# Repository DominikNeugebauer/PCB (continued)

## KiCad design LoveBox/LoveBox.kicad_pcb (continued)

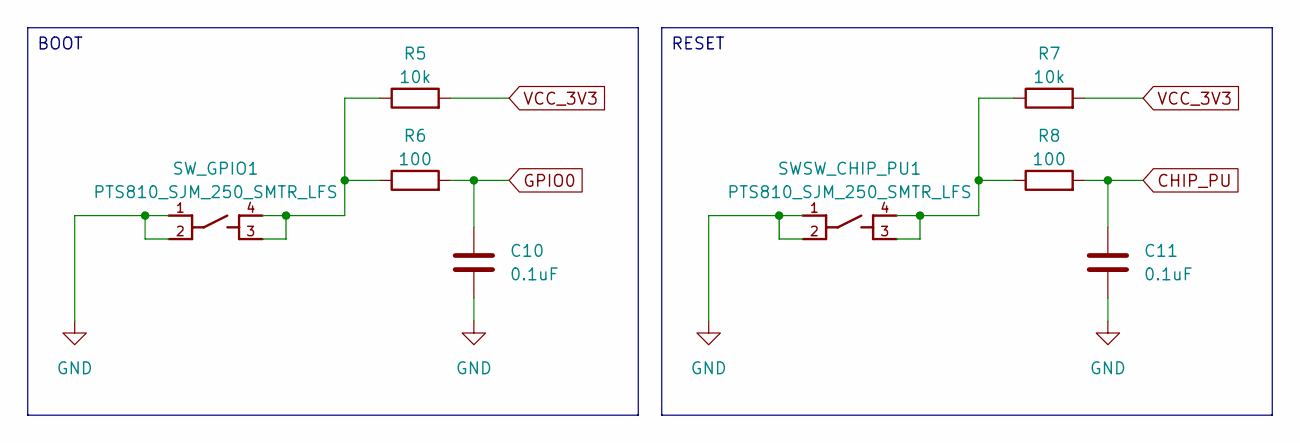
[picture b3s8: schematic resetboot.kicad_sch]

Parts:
C10, C11: 0.1uF; C_0603_1608Metric
R5, R7: 10k; R_0603_1608Metric
R6, R8: 100; R_0603_1608Metric
SWSW_CHIP_PU1: PTS810_SJM_250_SMTR_LFS
SW_GPIO1: PTS810_SJM_250_SMTR_LFS

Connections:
CHIP_PU: C11.1, R8.2; also elsewhere on the board
GND: C10.2, C11.2, SWSW_CHIP_PU1.1, SWSW_CHIP_PU1.2, SW_GPIO1.1, SW_GPIO1.2; also elsewhere on the board
GPIO0: C10.1, R6.2; also elsewhere on the board
unnamed 22: R5.1, R6.1, SW_GPIO1.3, SW_GPIO1.4; also elsewhere on the board
unnamed 23: R7.1, R8.1, SWSW_CHIP_PU1.3, SWSW_CHIP_PU1.4; also elsewhere on the board
VCC_3V3: R5.2, R7.2; also elsewhere on the board

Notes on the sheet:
RESET
BOOT

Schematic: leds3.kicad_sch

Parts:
C25, C38, C39, C40, C41, C42, C43, C44, C45, C46: 100nF; C_0603_1608Metric
R31: 330; R_0603_1608Metric
U27, U28, U29, U30, U31, U32, U33, U34, U35, U36: WS2812B; WS2812B_WDS

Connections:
GND: C25.2, C38.2, C39.2, C40.2, C41.2, C42.2, C43.2, C44.2, C45.2, C46.2, U27.3 (VSS), U28.3 (VSS), U29.3 (VSS), U30.3 (VSS), U31.3 (VSS), U32.3 (VSS), U33.3 (VSS), U34.3 (VSS), U35.3 (VSS), U36.3 (VSS); also elsewhere on the board
LEDS3: R31.1; also elsewhere on the board
LEDS4: U36.2 (DOUT); also elsewhere on the board
unnamed: R31.2, U27.4 (DIN)
unnamed: U27.2 (DOUT), U30.4 (DIN)
unnamed: U28.2 (DOUT), U31.4 (DIN)
unnamed: U29.2 (DOUT), U32.4 (DIN)
unnamed: U30.2 (DOUT), U33.4 (DIN)
unnamed: U31.2 (DOUT), U34.4 (DIN)
unnamed: U32.2 (DOUT), U35.4 (DIN)
unnamed: U35.2 (DOUT), U36.4 (DIN)
RE6: U28.4 (DIN), U33.2 (DOUT)
RE7: U29.4 (DIN), U34.2 (DOUT)
VCC_3V3: C25.1, C38.1, C39.1, C40.1, C41.1, C42.1, C43.1, C44.1, C45.1, C46.1, U27.1 (VDD), U28.1 (VDD), U29.1 (VDD), U30.1 (VDD), U31.1 (VDD), U32.1 (VDD), U33.1 (VDD), U34.1 (VDD), U35.1 (VDD), U36.1 (VDD); also elsewhere on the board

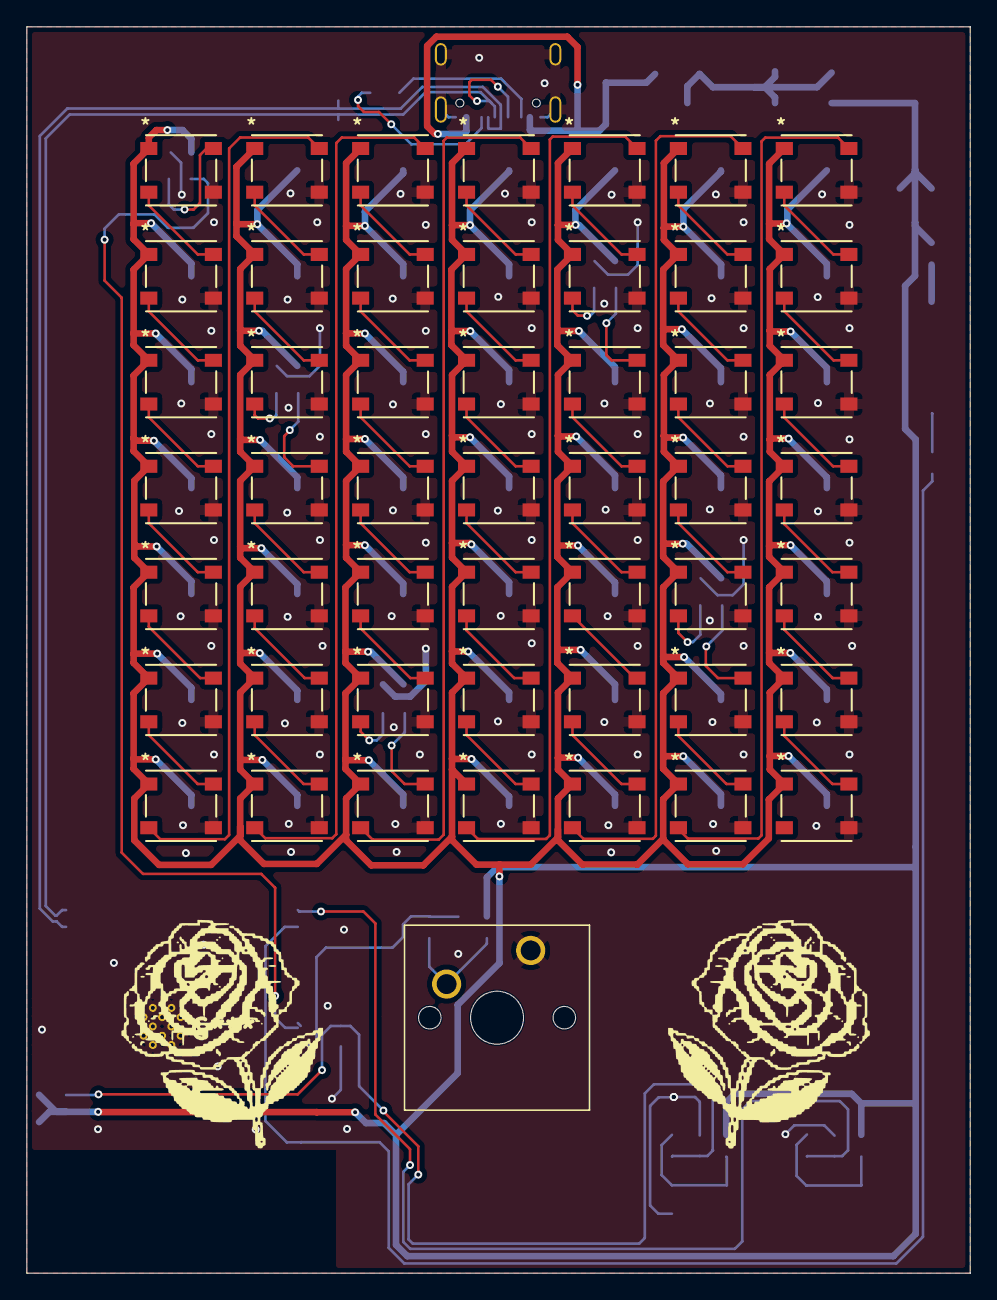
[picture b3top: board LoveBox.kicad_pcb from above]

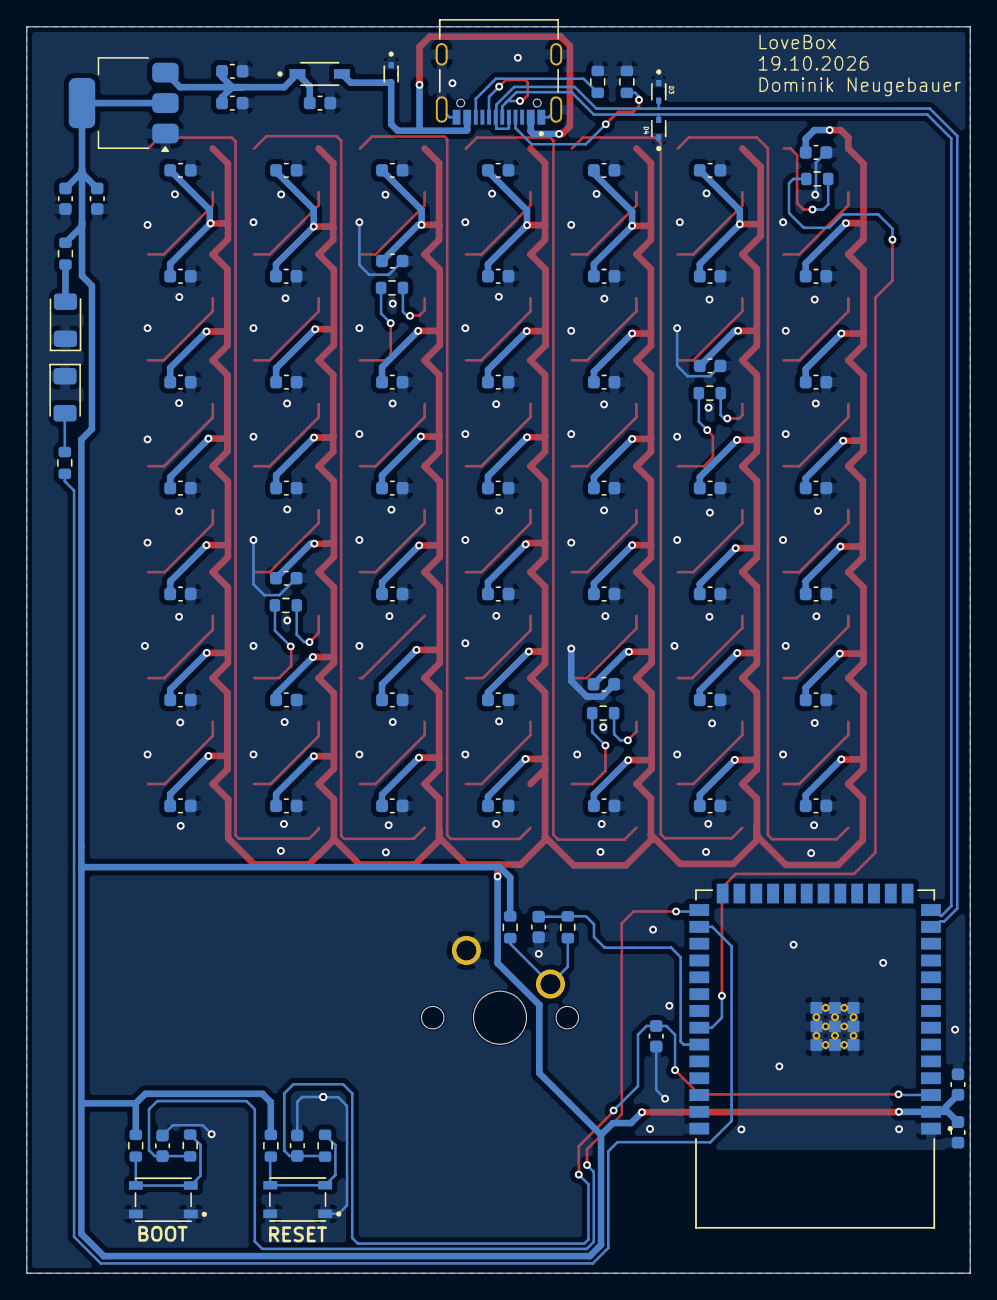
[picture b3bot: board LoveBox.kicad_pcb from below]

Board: 2 copper layers, 71.3 x 94.1 mm, 136 parts (86 on the bottom side), 71 nets.

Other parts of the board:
BOOT: PTS810_SJM_250_SMTR_LFS
RESET: PTS810_SJM_250_SMTR_LFS

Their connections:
GND: BOOT.1, BOOT.2, RESET.1, RESET.2; also elsewhere on the board
unnamed 22: BOOT.3, BOOT.4; also elsewhere on the board
unnamed 23: RESET.3, RESET.4; also elsewhere on the board

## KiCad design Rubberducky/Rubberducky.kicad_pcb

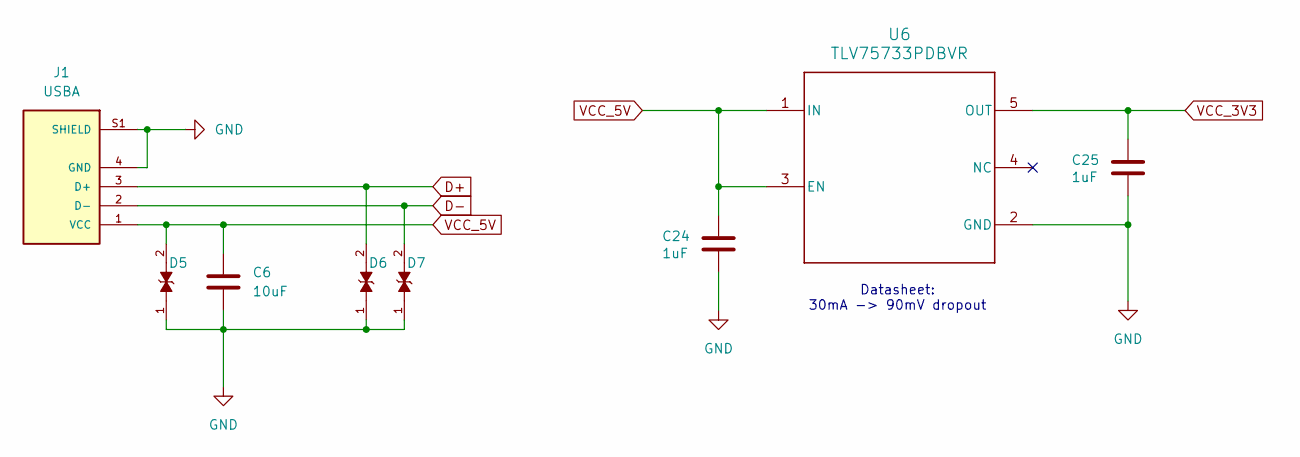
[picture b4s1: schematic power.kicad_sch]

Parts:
C6: 10uF; C_0603_1608Metric
C24, C25: 1uF; C_0603_1608Metric
D5, D6, D7: LESD5D5.0CT1G; PARTREV O
J1: USBA; USBA_Male_SMD; PARTREV D
U6: TLV75733PDBVR; SOT95P280X145-5N_TLV75733PDBVR

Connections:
D+: D6.2, J1.3 (D+); also elsewhere on the board
D-: D7.2, J1.2 (D-); also elsewhere on the board
GND: C6.2, C24.2, C25.2, D5.1, D6.1, D7.1, J1.4 (GND), J1.S1 (SHIELD), J1.S2 (SHIELD), U6.2 (GND); also elsewhere on the board
VCC_3V3: C25.1, U6.5 (OUT); also elsewhere on the board
VCC_5V: C6.1, C24.1, D5.2, J1.1 (VCC), U6.1 (IN), U6.3 (EN)

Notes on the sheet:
Datasheet: 30mA -> 90mV dropout

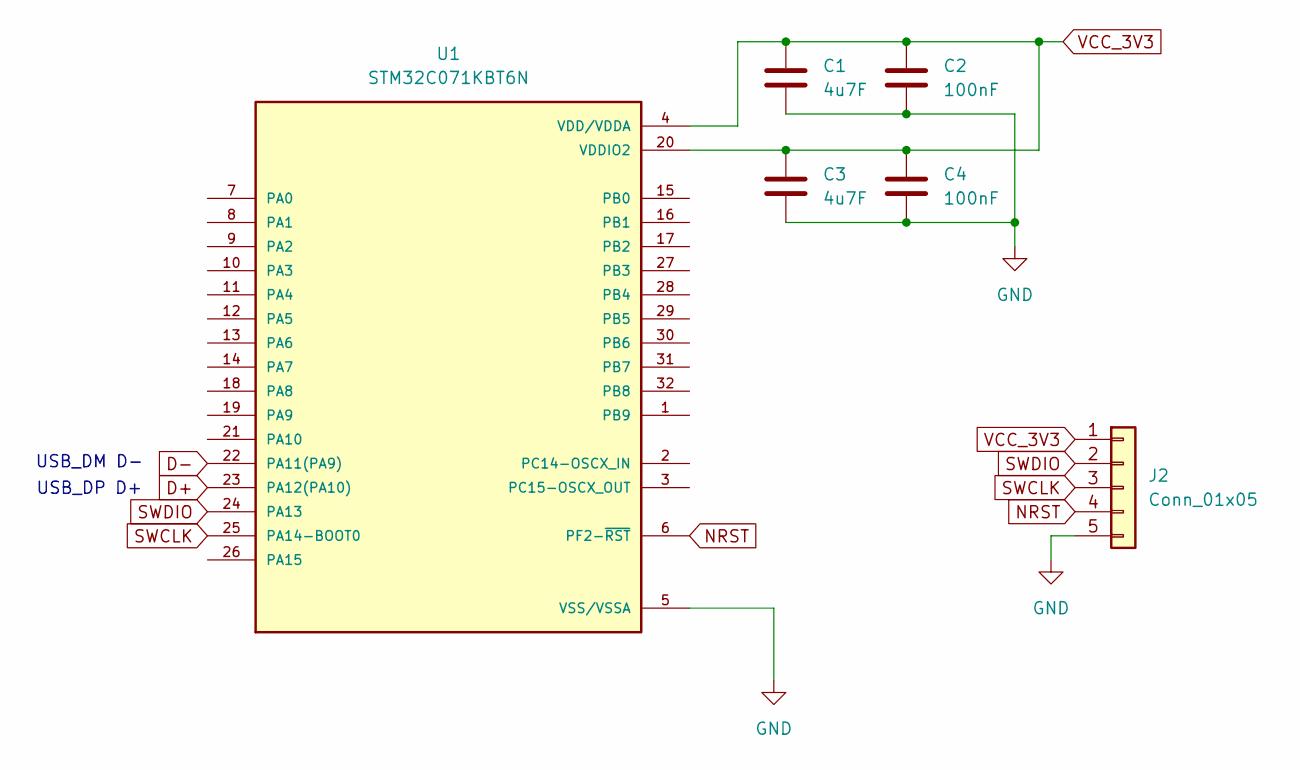
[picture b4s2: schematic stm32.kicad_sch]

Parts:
C1, C3: 4u7F; C_0603_1608Metric
C2, C4: 100nF; C_0603_1608Metric
J2: Conn_01x05; PinHeader_1x05_P2.54mm_Vertical
U1: STM32C071KBT6N; PARTREV 1

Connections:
D+: U1.23 (PA12(PA10)); also elsewhere on the board
D-: U1.22 (PA11(PA9)); also elsewhere on the board
GND: C1.2, C2.2, C3.2, C4.2, J2.5, U1.5 (VSS/VSSA); also elsewhere on the board
NRST: J2.4, U1.6 (PF2-~RST)
SWCLK: J2.3, U1.25 (PA14-BOOT0)
SWDIO: J2.2, U1.24 (PA13)
VCC_3V3: C1.1, C2.1, C3.1, C4.1, J2.1, U1.4 (VDD/VDDA), U1.20 (VDDIO2); also elsewhere on the board

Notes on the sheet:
USB_DM D-
USB_DP D+

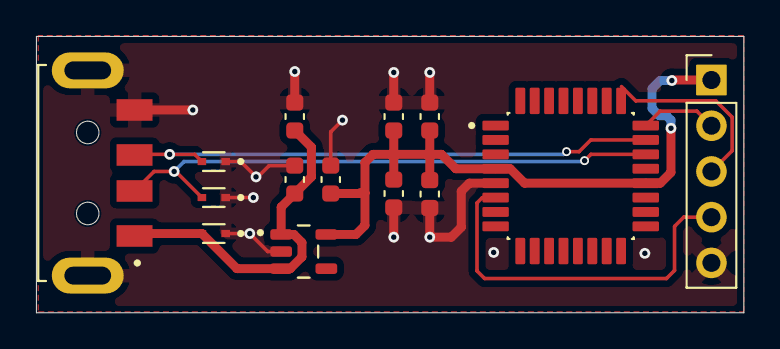
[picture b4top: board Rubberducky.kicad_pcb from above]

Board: 2 copper layers, 39.3 x 15.4 mm, 14 parts (0 on the bottom side), 8 nets.

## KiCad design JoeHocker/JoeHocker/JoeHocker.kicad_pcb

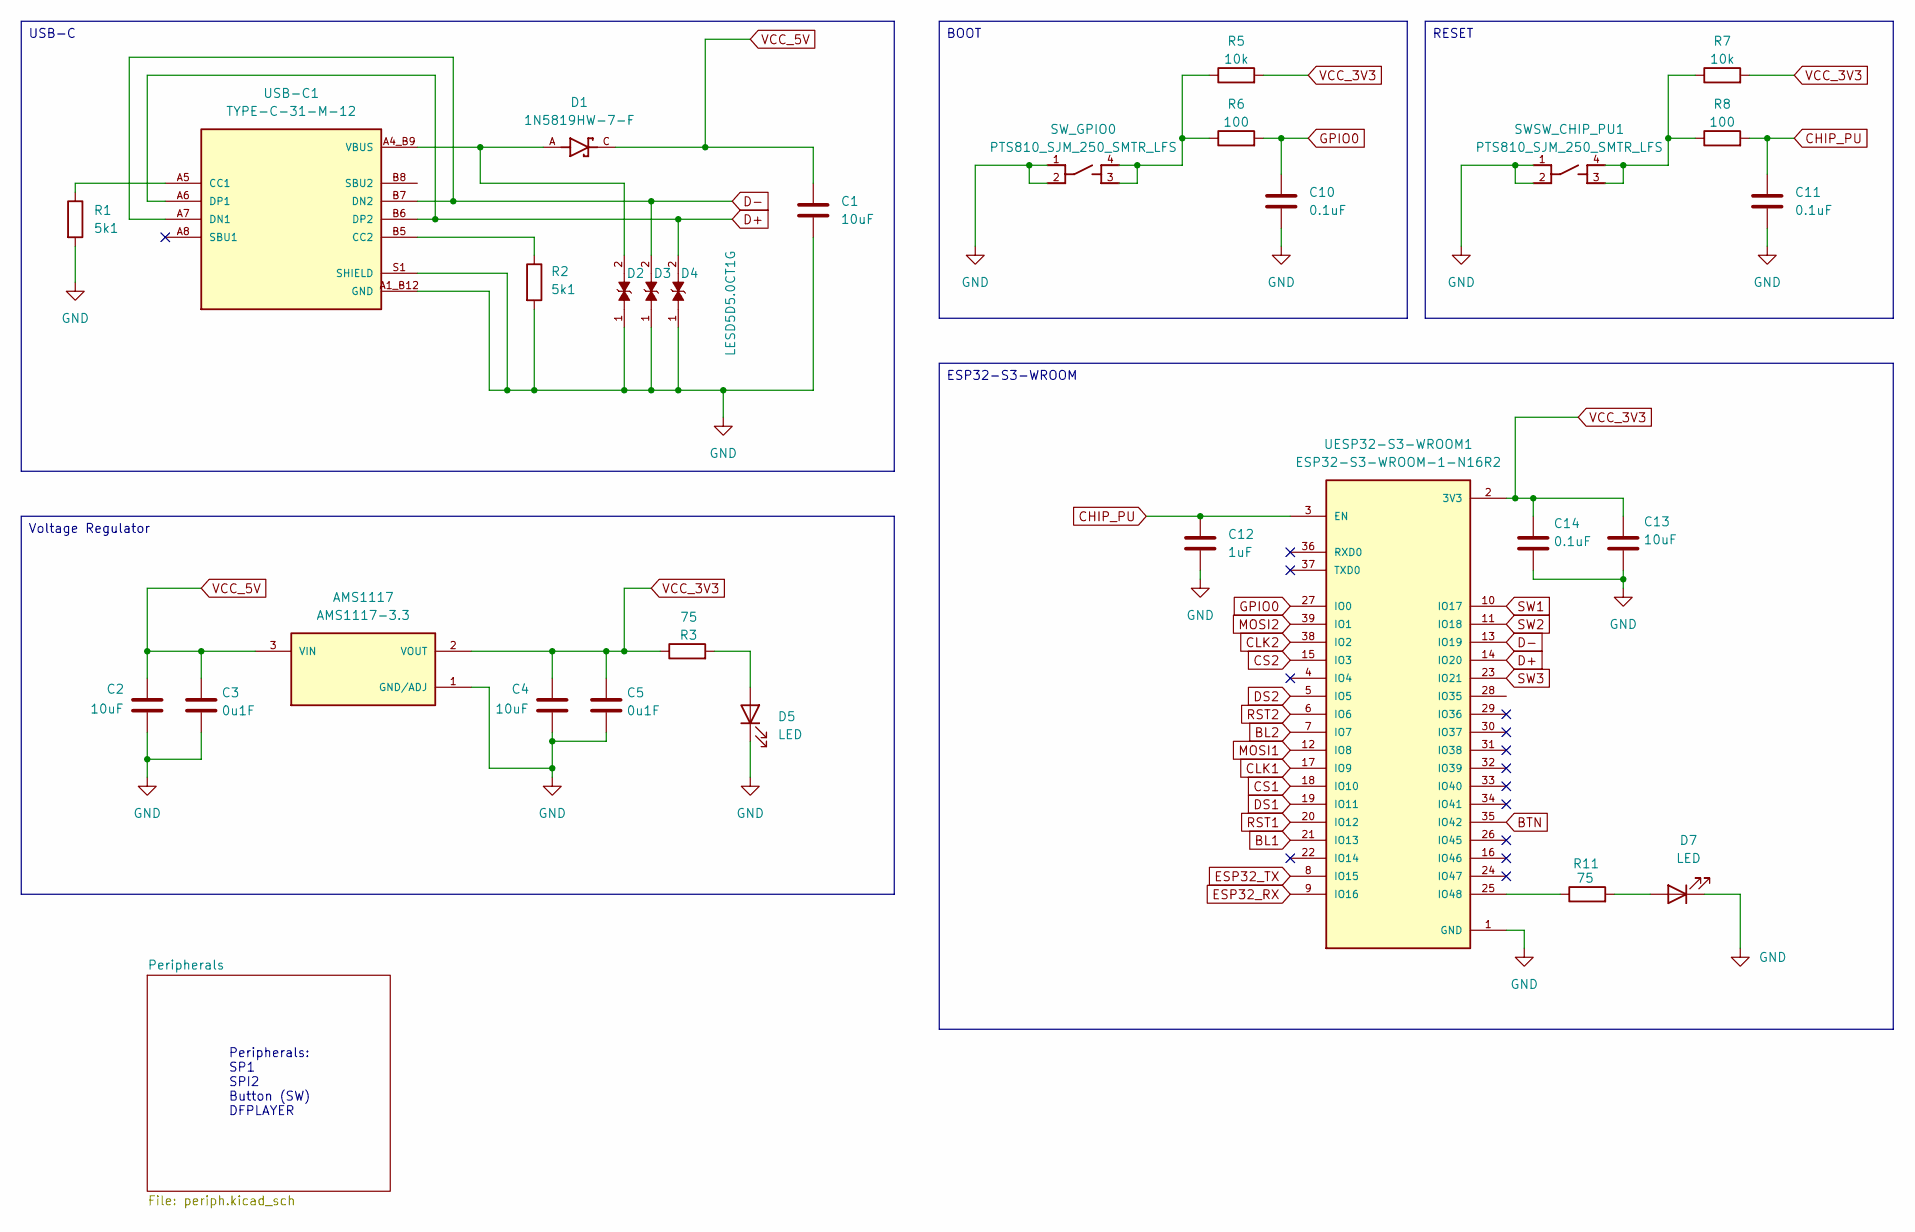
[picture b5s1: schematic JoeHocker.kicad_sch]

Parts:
AMS1117: AMS1117-3.3; SOT-223-3_TabPin2; PARTREV N/A
C1, C2, C4, C13: 10uF; C_0603_1608Metric
C3, C5: 0u1F; C_0603_1608Metric
C10, C11, C14: 0.1uF; C_0603_1608Metric
C12: 1uF; C_0603_1608Metric
D1: 1N5819HW-7-F; SOD3715X145N; PARTREV 18-2
D2, D3, D4: LESD5D5.0CT1G; TVS_LESD5D5.0CT1G; PARTREV O
D5, D7: LED; LED_1206_3216Metric
R1, R2: 5k1; R_0603_1608Metric
R3, R11: 75; R_0603_1608Metric
R5, R7: 10k; R_0603_1608Metric
R6, R8: 100; R_0603_1608Metric
SWSW_CHIP_PU1: PTS810_SJM_250_SMTR_LFS; SW_PTS810_SJM_250_SMTR_LFS
SW_GPIO0: PTS810_SJM_250_SMTR_LFS; SW_PTS810_SJM_250_SMTR_LFS
UESP32-S3-WROOM1: ESP32-S3-WROOM-1-N16R2; ESP32_S3_WROOM_N16R2_CUSTOM; PARTREV v1.0
USB-C1: TYPE-C-31-M-12; HRO_TYPE-C-31-M-12; PARTREV 2020.12.08

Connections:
BL1: UESP32-S3-WROOM1.21 (IO13); also elsewhere on the board
BL2: UESP32-S3-WROOM1.7 (IO7); also elsewhere on the board
BTN: UESP32-S3-WROOM1.35 (IO42); also elsewhere on the board
CHIP_PU: C11.1, C12.1, R8.2, UESP32-S3-WROOM1.3 (EN)
CLK1: UESP32-S3-WROOM1.17 (IO9); also elsewhere on the board
CLK2: UESP32-S3-WROOM1.38 (IO2); also elsewhere on the board
CS1: UESP32-S3-WROOM1.18 (IO10); also elsewhere on the board
CS2: UESP32-S3-WROOM1.15 (IO3); also elsewhere on the board
D+: D4.2, UESP32-S3-WROOM1.14 (IO20), USB-C1.A6 (DP1), USB-C1.B6 (DP2)
D-: D3.2, UESP32-S3-WROOM1.13 (IO19), USB-C1.A7 (DN1), USB-C1.B7 (DN2)
DS1: UESP32-S3-WROOM1.19 (IO11); also elsewhere on the board
DS2: UESP32-S3-WROOM1.5 (IO5); also elsewhere on the board
ESP32_RX: UESP32-S3-WROOM1.9 (IO16); also elsewhere on the board
ESP32_TX: UESP32-S3-WROOM1.8 (IO15); also elsewhere on the board
GND: AMS1117.1 (GND/ADJ), C1.2, C2.2, C3.2, C4.2, C5.2, C10.2, C11.2, C12.2, C13.2, C14.2, D2.1, D3.1, D4.1, D5.1 (K), D7.1 (K), R1.2, R2.2, SWSW_CHIP_PU1.1, SWSW_CHIP_PU1.2, SW_GPIO0.1, SW_GPIO0.2, UESP32-S3-WROOM1.1 (GND), UESP32-S3-WROOM1.40 (GND), UESP32-S3-WROOM1.41_1 (GND), UESP32-S3-WROOM1.41_2 (GND), UESP32-S3-WROOM1.41_3 (GND), UESP32-S3-WROOM1.41_4 (GND), UESP32-S3-WROOM1.41_5 (GND), UESP32-S3-WROOM1.41_6 (GND), UESP32-S3-WROOM1.41_7 (GND), UESP32-S3-WROOM1.41_8 (GND), UESP32-S3-WROOM1.41_9 (GND), UESP32-S3-WROOM1.41_10, UESP32-S3-WROOM1.41_11, UESP32-S3-WROOM1.41_12, UESP32-S3-WROOM1.41_13, UESP32-S3-WROOM1.41_14, UESP32-S3-WROOM1.41_15, UESP32-S3-WROOM1.41_16, UESP32-S3-WROOM1.41_17, UESP32-S3-WROOM1.41_18, UESP32-S3-WROOM1.41_19, UESP32-S3-WROOM1.41_20, UESP32-S3-WROOM1.41_21, USB-C1.A1_B12 (GND), USB-C1.B1_A12 (GND), USB-C1.S1 (SHIELD), USB-C1.S2 (SHIELD), USB-C1.S3 (SHIELD), USB-C1.S4 (SHIELD); also elsewhere on the board
GPIO0: C10.1, R6.2, UESP32-S3-WROOM1.27 (IO0)
MOSI1: UESP32-S3-WROOM1.12 (IO8); also elsewhere on the board
MOSI2: UESP32-S3-WROOM1.39 (IO1); also elsewhere on the board
unnamed: D5.2 (A), R3.2
unnamed: D7.2 (A), R11.2
unnamed 22: R5.1, R6.1, SW_GPIO0.3, SW_GPIO0.4; also elsewhere on the board
unnamed 23: R7.1, R8.1, SWSW_CHIP_PU1.3, SWSW_CHIP_PU1.4; also elsewhere on the board
unnamed: R11.1, UESP32-S3-WROOM1.25 (IO48)
unnamed: R1.1, USB-C1.A5 (CC1)
unnamed: R2.1, USB-C1.B5 (CC2)
RST1: UESP32-S3-WROOM1.20 (IO12); also elsewhere on the board
RST2: UESP32-S3-WROOM1.6 (IO6); also elsewhere on the board
SW1: UESP32-S3-WROOM1.10 (IO17); also elsewhere on the board
SW2: UESP32-S3-WROOM1.11 (IO18); also elsewhere on the board
SW3: UESP32-S3-WROOM1.23 (IO21); also elsewhere on the board
VBUS: D1.A, D2.2, USB-C1.A4_B9 (VBUS), USB-C1.B4_A9 (VBUS)
VCC_3V3: AMS1117.2 (VOUT), C4.1, C5.1, C13.1, C14.1, R3.1, R5.2, R7.2, UESP32-S3-WROOM1.2 (3V3); also elsewhere on the board
VCC_5V: AMS1117.3 (VIN), C1.1, C2.1, C3.1, D1.C

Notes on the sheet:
Peripherals: SP1 SPI2 Button (SW) DFPLAYER
BOOT
ESP32-S3-WROOM
Voltage Regulator
RESET
USB-C

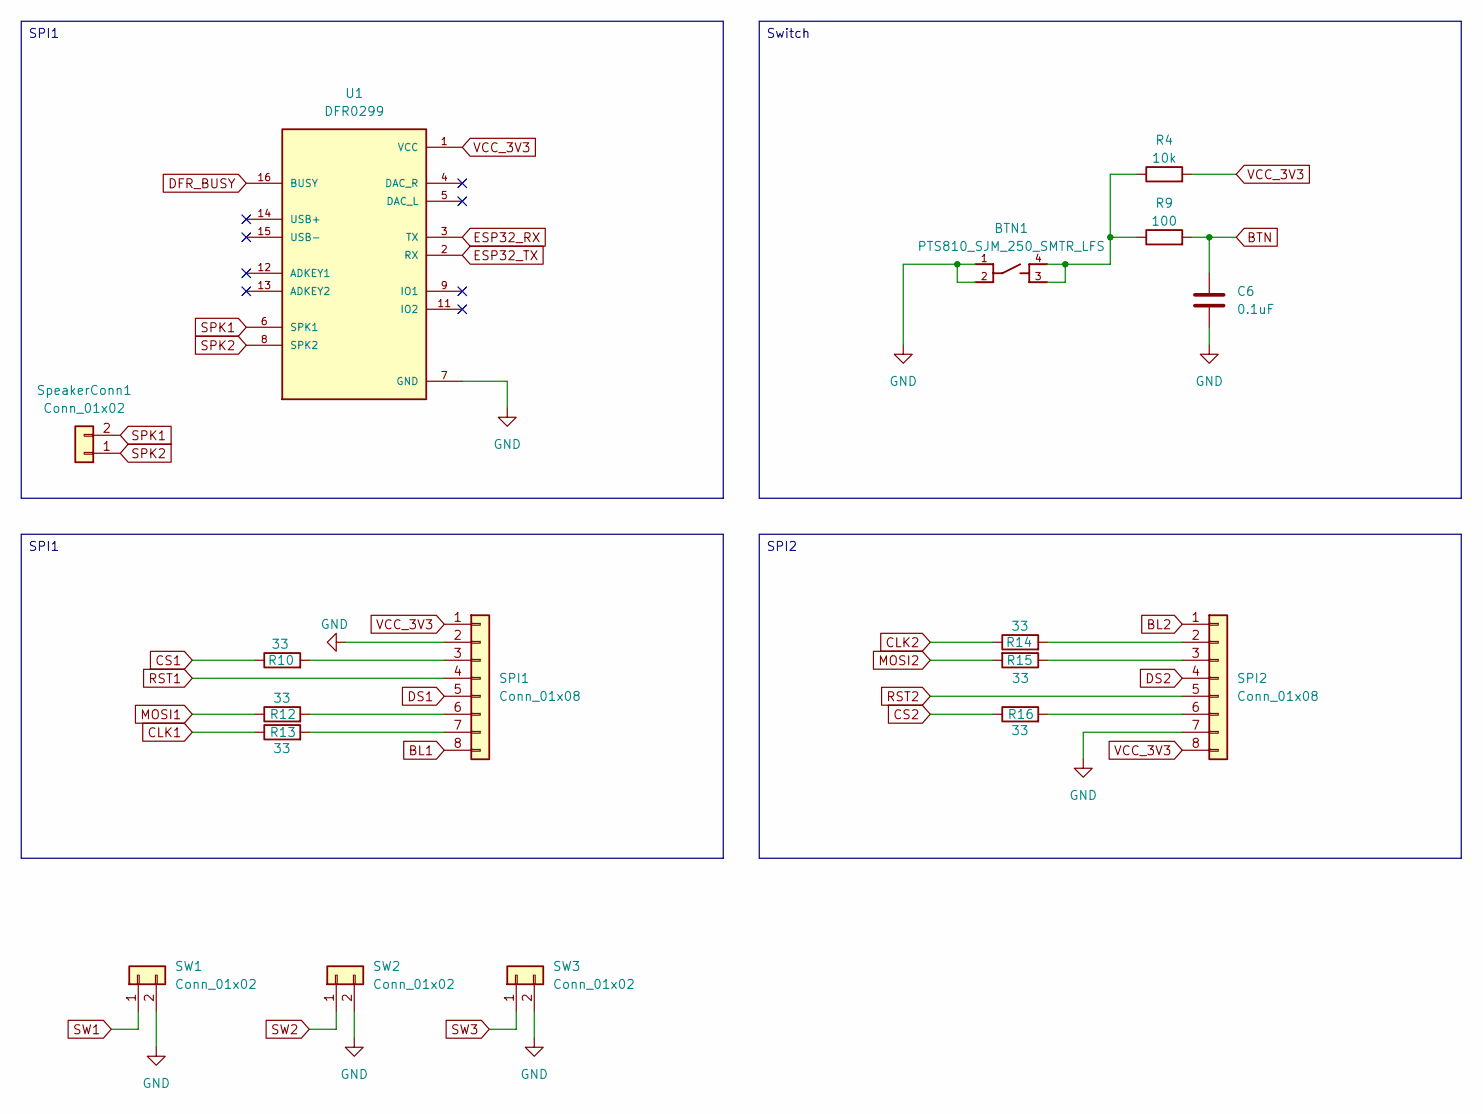
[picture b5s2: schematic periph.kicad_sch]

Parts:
BTN1: PTS810_SJM_250_SMTR_LFS; SW_PTS810_SJM_250_SMTR_LFS
C6: 0.1uF; C_0603_1608Metric
R4: 10k; R_0603_1608Metric
R9: 100; R_0603_1608Metric
R10, R12, R13, R14, R15, R16: 33; R_0603_1608Metric
SPI1, SPI2: Conn_01x08; PinHeader_1x08_P2.54mm_Vertical
SW1, SW2, SW3: Conn_01x02; PinHeader_1x02_P2.54mm_Vertical
SpeakerConn1: Conn_01x02; PinHeader_1x02_P2.54mm_Vertical
U1: DFR0299; MODULE_DFR029_DFPLAYER

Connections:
BL1: SPI1.8; also elsewhere on the board
BL2: SPI2.1; also elsewhere on the board
BTN: C6.1, R9.2; also elsewhere on the board
CLK1: R13.1; also elsewhere on the board
CLK2: R14.1; also elsewhere on the board
CS1: R10.1; also elsewhere on the board
CS2: R16.1; also elsewhere on the board
DFR_BUSY: U1.16 (BUSY)
DS1: SPI1.5; also elsewhere on the board
DS2: SPI2.4; also elsewhere on the board
ESP32_RX: U1.3 (TX); also elsewhere on the board
ESP32_TX: U1.2 (RX); also elsewhere on the board
GND: BTN1.1, BTN1.2, C6.2, SPI1.2, SPI2.7, SW1.2, SW2.2, SW3.2, U1.7 (GND), U1.10 (GND); also elsewhere on the board
MOSI1: R12.1; also elsewhere on the board
MOSI2: R15.2; also elsewhere on the board
unnamed 19: BTN1.3, BTN1.4, R4.1, R9.1; also elsewhere on the board
unnamed: R10.2, SPI1.3
unnamed: R12.2, SPI1.6
unnamed: R13.2, SPI1.7
unnamed: R14.2, SPI2.2
unnamed: R15.1, SPI2.3
unnamed: R16.2, SPI2.6
RST1: SPI1.4; also elsewhere on the board
RST2: SPI2.5; also elsewhere on the board
SPK1: SpeakerConn1.2, U1.6 (SPK1)
SPK2: SpeakerConn1.1, U1.8 (SPK2)
SW1: SW1.1; also elsewhere on the board
SW2: SW2.1; also elsewhere on the board
SW3: SW3.1; also elsewhere on the board
VCC_3V3: R4.2, SPI1.1, SPI2.8, U1.1 (VCC); also elsewhere on the board

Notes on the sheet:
SPI1
SPI2
Switch

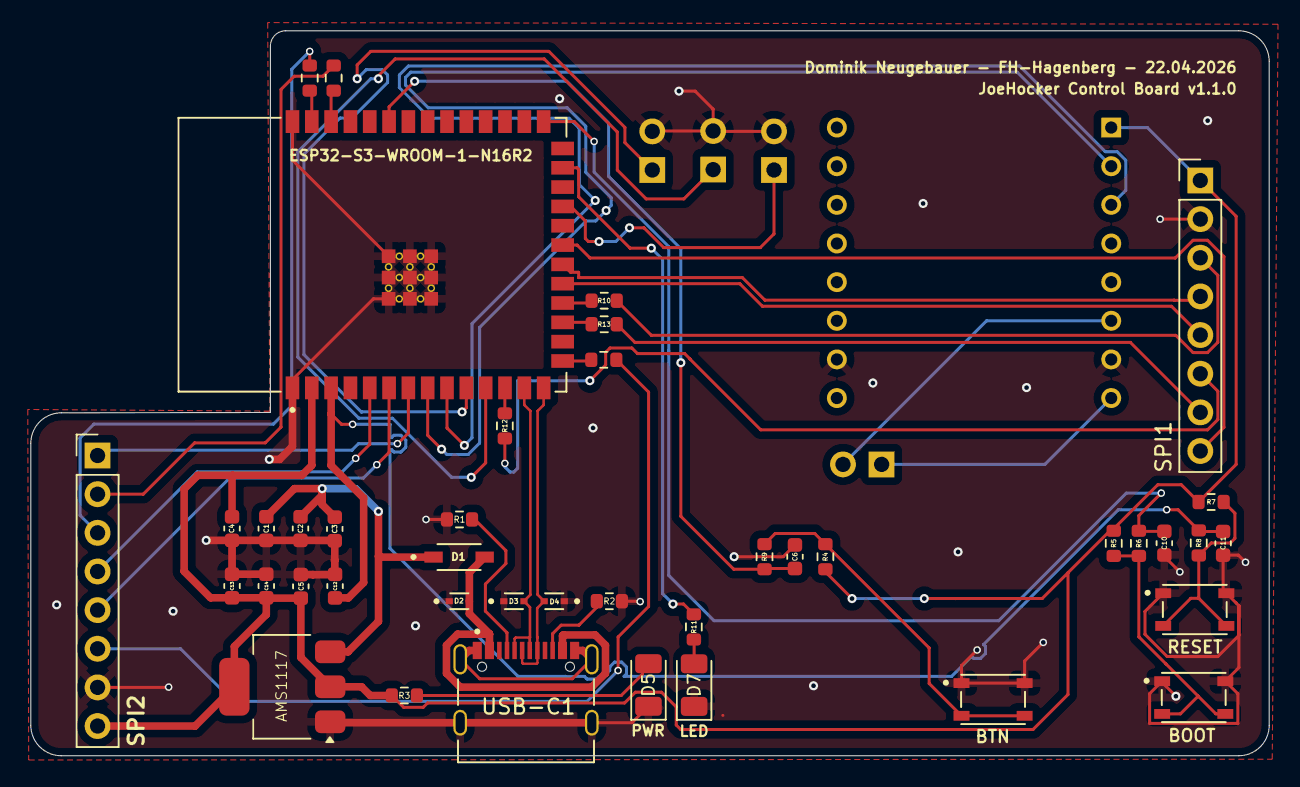
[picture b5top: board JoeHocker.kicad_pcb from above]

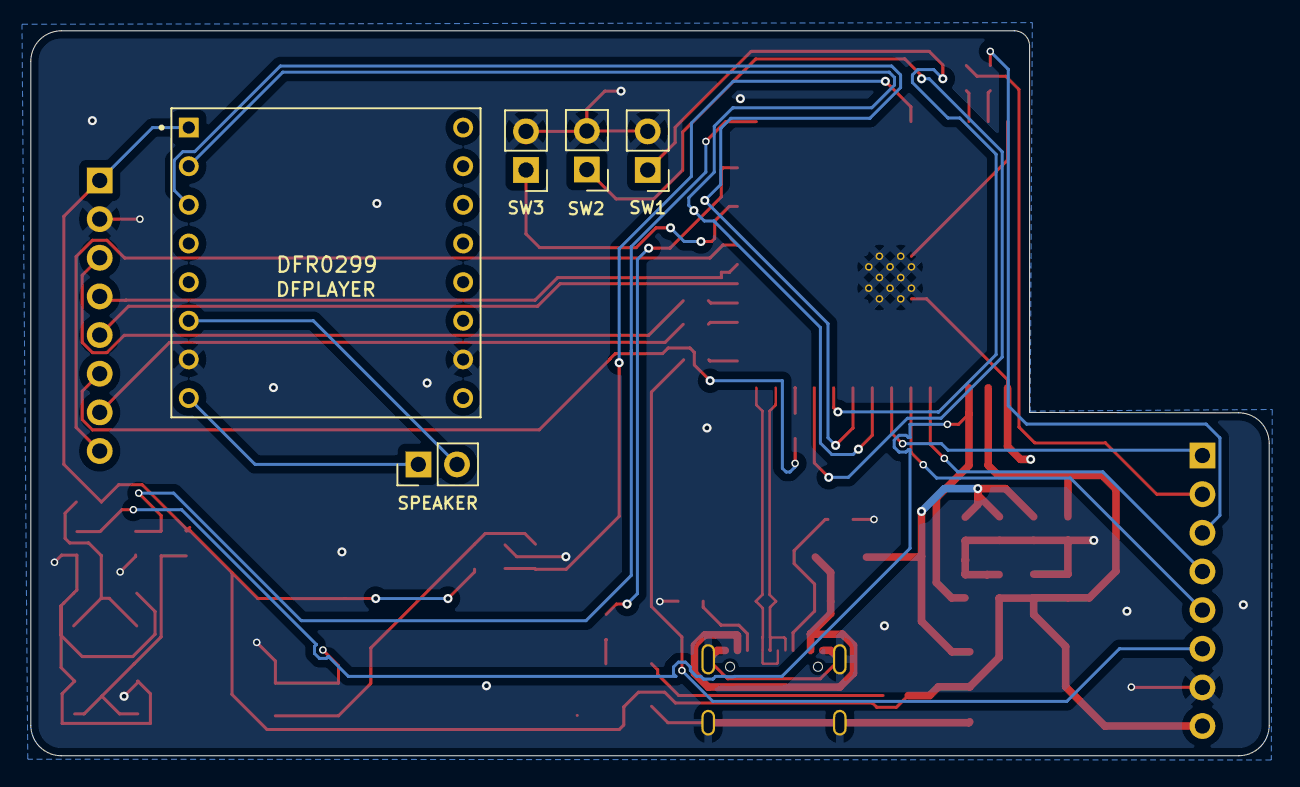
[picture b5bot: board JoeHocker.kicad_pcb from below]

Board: 4 copper layers, 81.4 x 47.6 mm, 46 parts (5 on the bottom side), 42 nets.

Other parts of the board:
BOOT: PTS810_SJM_250_SMTR_LFS; SW_PTS810_SJM_250_SMTR_LFS
BTN: PTS810_SJM_250_SMTR_LFS; SW_PTS810_SJM_250_SMTR_LFS
RESET: PTS810_SJM_250_SMTR_LFS; SW_PTS810_SJM_250_SMTR_LFS

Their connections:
GND: BOOT.1, BOOT.2, BTN.1, BTN.2, RESET.1, RESET.2; also elsewhere on the board
unnamed 19: BTN.3, BTN.4; also elsewhere on the board
unnamed 22: BOOT.3, BOOT.4; also elsewhere on the board
unnamed 23: RESET.3, RESET.4; also elsewhere on the board

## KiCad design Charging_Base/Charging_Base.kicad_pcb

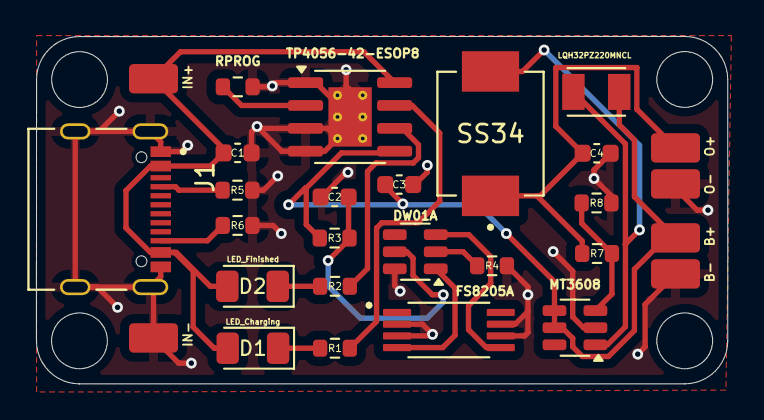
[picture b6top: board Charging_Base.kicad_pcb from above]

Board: 2 copper layers, 38.4 x 19.3 mm, 28 parts (0 on the bottom side), 17 nets.

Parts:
B+: Solder; Custom_Pad
B-: Solder; Custom_Pad
C1: 10uF; C_0603_1608Metric
C2: 0.1uF; C_0603_1608Metric
C3, C4: 22uF; C_0603_1608Metric
D1: LED_Charging; LED_1206_3216Metric
D2: LED_Finished; LED_1206_3216Metric
D3: SS34; DIODE_SCHOTTKY_S34_DIOM7959X265N
IN+: Solder; Custom_Pad
IN-: Solder; Custom_Pad
J1: TYPE-C-31-M-12; USBC_Connector_HRO_TYPE-C-31-M-12
L1: LQH32PZ220MNCL; INDUCTOR_LQH32PZ220MNCL
O+: Solder; Custom_Pad
O-: Solder; Custom_Pad
Q1: FS8205A; FS8205A_SOP65P640X120-8N
R1, R2: 1k; R_0603_1608Metric
R3: 470; R_0603_1608Metric
R4: 2k; R_0603_1608Metric
R5, R6: 5k1; R_0603_1608Metric
R7: 75k; R_0603_1608Metric
R8: 10k; R_0603_1608Metric
RPROG: 2k; R_0603_1608Metric
U1: TP4056-42-ESOP8; SOIC-8-1EP_3.9x4.9mm_P1.27mm_EP2.41x3.3mm_ThermalVias
U2: DW01A; SOT-23-6
U3: MT3608; SOT-23-6

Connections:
GND: B-.1, C1.2, C2.2, C3.2, C4.2, IN-.1, J1.A1_B12 (GND), J1.B1_A12 (GND), J1.S1 (SHIELD), J1.S2 (SHIELD), J1.S3 (SHIELD), J1.S4 (SHIELD), O-.1, Q1.2, Q1.3, Q1.6, Q1.7, R4.2, R5.2, R6.2, R8.2, RPROG.2, U1.1 (TEMP), U1.3 (GND), U1.4 (V_{CC}), U1.9 (EPAD), U2.6 (GND), U3.2 (GND)
unnamed: C4.1, D3.C, O+.1, R7.1
unnamed: D1.1 (K), R1.1
unnamed: D2.1 (K), R2.1
unnamed: J1.A5 (CC1), R5.1
unnamed: J1.B5 (CC2), R6.1
unnamed: RPROG.1, U1.2 (PROG)
unnamed: R1.2, U1.7 (~CHRG)
unnamed: R2.2, U1.6 (~STDBY)
unnamed: R4.1, U2.2 (CS)
unnamed: Q1.5, U2.3 (OC)
unnamed: Q1.4, U2.1 (OD)
unnamed: C2.1, R3.1, U2.5 (VCC)
unnamed: R7.2, R8.1, U3.3 (FB)
unnamed: D3.A, L1.2, U3.1 (SW)
OUT_NOBOOST: B+.1, C3.1, L1.1, R3.2, U1.5 (BAT), U3.4 (EN), U3.5 (IN)
VBUS: C1.1, D1.2 (A), D2.2 (A), IN+.1, J1.A4_B9 (VBUS), J1.B4_A9 (VBUS), U1.8 (CE)

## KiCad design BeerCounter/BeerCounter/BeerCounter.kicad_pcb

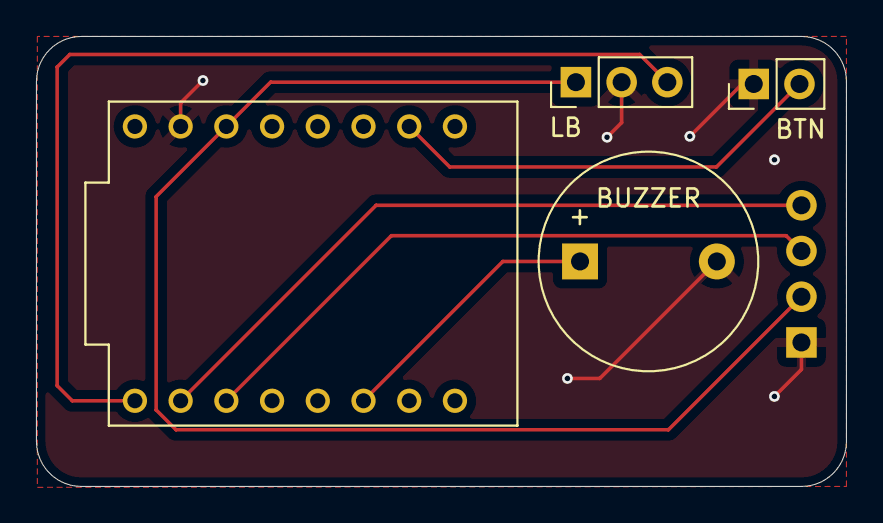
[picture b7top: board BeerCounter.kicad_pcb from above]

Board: 2 copper layers, 45.0 x 25.0 mm, 5 parts (1 on the bottom side), 7 nets.

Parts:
BTN: Conn_01x02; PinHeader_1x02_P2.54mm_Vertical
BUZZER: Buzzer; Buzzer_12x9.5RM7.6
DISPLAY: Conn_01x04; PinHeader_1x04_P2.54mm_Vertical
LB: Conn_01x03; PinHeader_1x03_P2.54mm_Vertical
U1: ESP32-C3_SUPERMINI_TH; MODULE_ESP32-C3_SUPERMINI_TH

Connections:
3V3: DISPLAY.2, LB.1, U1.3.3 (3V3)
BTN: BTN.2, U1.1 (GPIO1)
BUZZER: BUZZER.1 (+), U1.10 (GPIO10)
GND: BTN.1, BUZZER.2 (-), DISPLAY.1, LB.2, U1.G (GND)
LIGHT_BARRIER: LB.3, U1.5 (GPIO5)
SCL: DISPLAY.3, U1.7 (GPIO7)
SDA: DISPLAY.4, U1.6 (GPIO6)

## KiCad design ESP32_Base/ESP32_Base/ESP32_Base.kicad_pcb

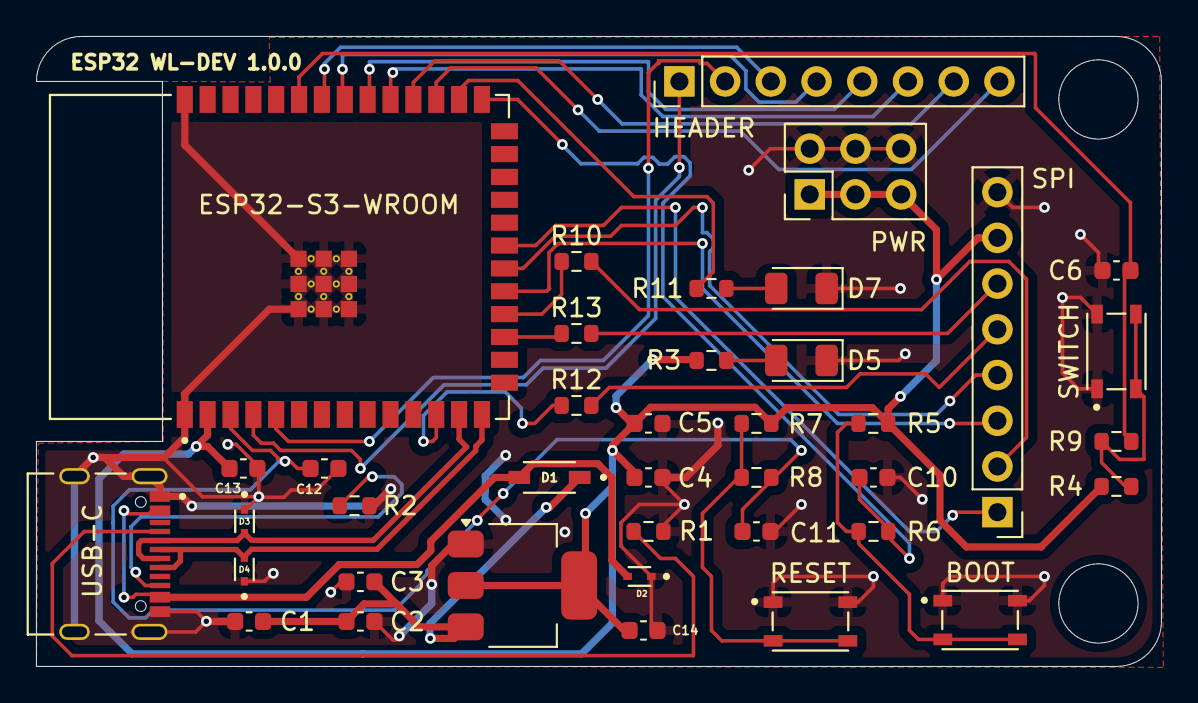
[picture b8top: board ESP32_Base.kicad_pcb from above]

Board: 2 copper layers, 62.5 x 35.0 mm, 39 parts (0 on the bottom side), 34 nets.

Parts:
AMS1117: AMS1117-3.3; SOT-223-3_TabPin2
BOOT: PTS810_SJM_250_SMTR_LFS; SW_PTS810_SJM_250_SMTR_LFS
C1, C2, C4, C13: 10uF; C_0603_1608Metric
C3, C5: 0u1F; C_0603_1608Metric
C6, C10, C11, C14: 0.1uF; C_0603_1608Metric
C12: 1uF; C_0603_1608Metric
D1: 1N5819HW-7-F; SOD3715X145N
D2, D3, D4: LESD5D5.0CT1G; TVS_LESD5D5.0CT1G
D5: PWR; LED_1206_3216Metric
D7: LED; LED_1206_3216Metric
ESP32-S3-WROOM: ESP32-S3-WROOM-1-N16R2; ESP32_S3_WROOM_N16R2_CUSTOM
HEADER: Conn_01x08; PinHeader_1x08_P2.54mm_Vertical
PWR: Conn_02x03_Odd_Even; PinHeader_2x03_P2.54mm_Vertical
R1, R2: 5k1; R_0603_1608Metric
R3, R11: 75; R_0603_1608Metric
R4, R5, R7: 10k; R_0603_1608Metric
R6, R8, R9: 100; R_0603_1608Metric
R10, R12, R13: 33; R_0603_1608Metric
RESET: PTS810_SJM_250_SMTR_LFS; SW_PTS810_SJM_250_SMTR_LFS
SPI: Conn_01x08; PinHeader_1x08_P2.54mm_Vertical
SWITCH: PTS810_SJM_250_SMTR_LFS; SW_PTS810_SJM_250_SMTR_LFS
USB-C: TYPE-C-31-M-12; HRO_TYPE-C-31-M-12

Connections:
BL: ESP32-S3-WROOM.21 (IO13), SPI.1
CHIP_PU: C11.1, C12.1, ESP32-S3-WROOM.3 (EN), R8.2
CLK: ESP32-S3-WROOM.17 (IO9), R13.1
CS: ESP32-S3-WROOM.18 (IO10), R10.1
D+: D4.2, ESP32-S3-WROOM.14 (IO20), USB-C.A6 (DP1), USB-C.B6 (DP2)
D-: D3.2, ESP32-S3-WROOM.13 (IO19), USB-C.A7 (DN1), USB-C.B7 (DN2)
DS: ESP32-S3-WROOM.19 (IO11), SPI.3
GND: AMS1117.1 (GND/ADJ), BOOT.1, BOOT.2, C1.2, C2.2, C3.2, C4.2, C5.2, C6.2, C10.2, C11.2, C12.2, C13.2, C14.2, D2.1, D3.1, D4.1, D5.1 (K), D7.1 (K), ESP32-S3-WROOM.1 (GND), ESP32-S3-WROOM.40 (GND), ESP32-S3-WROOM.41_1 (GND), ESP32-S3-WROOM.41_2 (GND), ESP32-S3-WROOM.41_3 (GND), ESP32-S3-WROOM.41_4 (GND), ESP32-S3-WROOM.41_5 (GND), ESP32-S3-WROOM.41_6 (GND), ESP32-S3-WROOM.41_7 (GND), ESP32-S3-WROOM.41_8 (GND), ESP32-S3-WROOM.41_9 (GND), ESP32-S3-WROOM.41_10, ESP32-S3-WROOM.41_11, ESP32-S3-WROOM.41_12, ESP32-S3-WROOM.41_13, ESP32-S3-WROOM.41_14, ESP32-S3-WROOM.41_15, ESP32-S3-WROOM.41_16, ESP32-S3-WROOM.41_17, ESP32-S3-WROOM.41_18, ESP32-S3-WROOM.41_19, ESP32-S3-WROOM.41_20, ESP32-S3-WROOM.41_21, PWR.2, PWR.4, PWR.6, R1.2, R2.2, RESET.1, RESET.2, SPI.8, SWITCH.1, SWITCH.2, USB-C.A1_B12 (GND), USB-C.B1_A12 (GND), USB-C.S1 (SHIELD), USB-C.S2 (SHIELD), USB-C.S3 (SHIELD), USB-C.S4 (SHIELD)
GPIO0: C10.1, ESP32-S3-WROOM.27 (IO0), R6.2
IO36: ESP32-S3-WROOM.29 (IO36), HEADER.8
IO37: ESP32-S3-WROOM.30 (IO37), HEADER.7
IO38: ESP32-S3-WROOM.31 (IO38), HEADER.6
IO39: ESP32-S3-WROOM.32 (IO39), HEADER.5
IO40: ESP32-S3-WROOM.33 (IO40), HEADER.4
IO41: ESP32-S3-WROOM.34 (IO41), HEADER.3
MOSI: ESP32-S3-WROOM.12 (IO8), R12.1
unnamed: D5.2 (A), R3.2
unnamed: D7.2 (A), R11.2
unnamed: R4.1, R9.1, SWITCH.3, SWITCH.4
unnamed: BOOT.3, BOOT.4, R5.1, R6.1
unnamed: R7.1, R8.1, RESET.3, RESET.4
unnamed: R10.2, SPI.2
unnamed: R12.2, SPI.5
unnamed: R13.2, SPI.6
unnamed: ESP32-S3-WROOM.28 (IO35), R11.1
unnamed: R1.1, USB-C.A5 (CC1)
unnamed: R2.1, USB-C.B5 (CC2)
RST: ESP32-S3-WROOM.20 (IO12), SPI.4
SCL: ESP32-S3-WROOM.4 (IO4), HEADER.1
SDA: ESP32-S3-WROOM.5 (IO5), HEADER.2
SW: C6.1, ESP32-S3-WROOM.35 (IO42), R9.2
VBUS: D1.A, D2.2, USB-C.A4_B9 (VBUS), USB-C.B4_A9 (VBUS)
VCC_3V3: AMS1117.2 (VOUT), C4.1, C5.1, C13.1, C14.1, ESP32-S3-WROOM.2 (3V3), PWR.1, PWR.3, PWR.5, R3.1, R4.2, R5.2, R7.2, SPI.7
VCC_5V: AMS1117.3 (VIN), C1.1, C2.1, C3.1, D1.C
